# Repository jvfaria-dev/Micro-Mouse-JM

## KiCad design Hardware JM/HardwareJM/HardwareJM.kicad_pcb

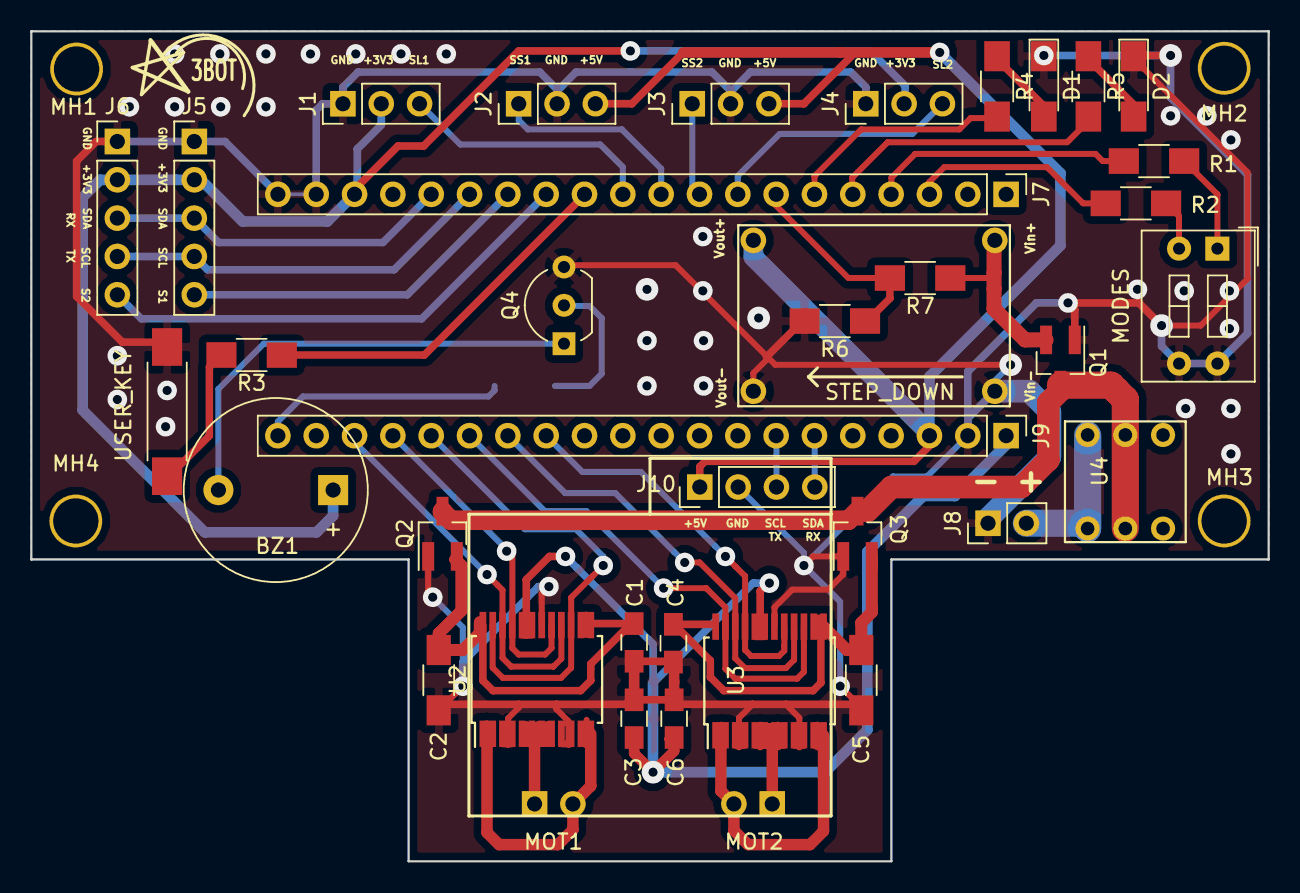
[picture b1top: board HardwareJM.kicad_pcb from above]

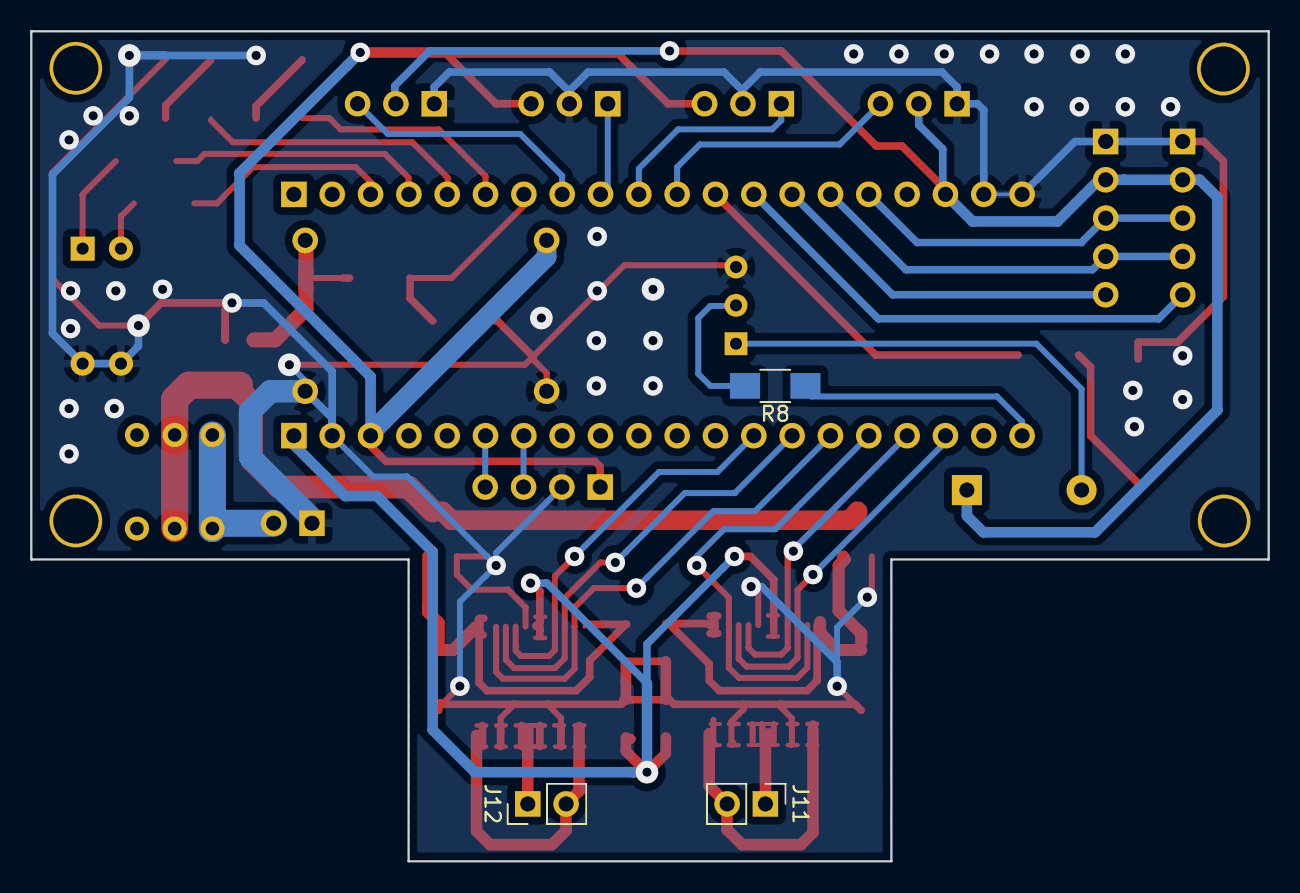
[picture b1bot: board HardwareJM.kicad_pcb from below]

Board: 2 copper layers, 82.0 x 55.0 mm, 43 parts (3 on the bottom side), 42 nets.

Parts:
BZ1: Buzzer; Buzzer_12x9.5RM7.6
C1, C3, C4, C6: C; C_0805_HandSoldering
C2, C5: CP1; C_1206_HandSoldering
D1, D2: LED; LED_1206_HandSoldering
J1: S_LINHA1; Pin_Header_Straight_1x03_Pitch2.54mm
J2: S_SHARP1; Pin_Header_Straight_1x03_Pitch2.54mm
J3: S_SHARP2; Pin_Header_Straight_1x03_Pitch2.54mm
J4: S_LINHA2; Pin_Header_Straight_1x03_Pitch2.54mm
J5: S_LASER1; Pin_Header_Straight_1x05_Pitch2.54mm
J6: S_LASER2; Pin_Header_Straight_1x05_Pitch2.54mm
J7, J9: Conn_01x20; Socket_Strip_Straight_1x20_Pitch2.54mm
J8: BAT; Pin_Header_Straight_1x02_Pitch2.54mm
J10: Conn_01x04; Socket_Strip_Straight_1x04_Pitch2.54mm
J11: MOT1; Pin_Header_Straight_1x02_Pitch2.54mm
J12: MOT2; Pin_Header_Straight_1x02_Pitch2.54mm
MH1: 1; SolderWirePad_single_1-2mmDrill
MH2: 2; SolderWirePad_single_1-2mmDrill
MH3: 3; SolderWirePad_single_1-2mmDrill
MH4: 4; SolderWirePad_single_1-2mmDrill
MODES: SW_DIP_x02; SW_DIP_x2_W7.62mm_Slide
Q1, Q2, Q3: BC817; SOT-23_Handsoldering
Q4: BC337; TO-92_Inline_Wide
R1, R2, R3, R4, R5, R6, R7, R8: R; R_1206_HandSoldering
STEP_DOWN: Step_sown; Step_down
U2, U3: TB6612FNG; SSOP-24_5.3x8.2mm_Pitch0.65mm
U4: KEY
USER_KEY: USER_KEY; SW_SPST_REED_CT05-XXXX-G1

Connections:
+3V3: BZ1.1, C3.1, C6.1, J1.2, J4.2, J5.2, J6.2, J7.18, J9.1, U2.19, U2.20, U3.19, U3.20
+5V: J2.3, J3.3, J9.3, J10.1, STEP_DOWN.4
/S1: J5.5, J7.14
/S2: J6.5, J7.13
/SCL: J5.4, J6.4, J7.15
/SDA: J5.3, J6.3, J7.16
/V+: Q1.2, R7.1, STEP_DOWN.1
/VBAT+: Q1.3, Q2.3, Q3.3, U4.2
/VMOT1: C1.1, C2.1, Q2.2, U2.13, U2.14, U2.24
/VMOT2: C4.1, C5.1, Q3.2, U3.13, U3.14, U3.24
GND: C1.2, C2.2, C3.2, C4.2, C5.2, C6.2, D1.1, D2.1, J1.1, J2.2, J3.2, J4.1, J5.1, J6.1, J7.19, J7.20, J8.1, J9.2, J10.2, MODES.3, MODES.4, Q1.1, Q2.1, Q3.1, Q4.3, R6.2, STEP_DOWN.2, STEP_DOWN.3, U2.3, U2.4, U2.9, U2.10, U2.18, U3.3, U3.4, U3.9, U3.10, U3.18, USER_KEY.1
unnamed: BZ1.2, Q4.1
unnamed: D1.2, R4.1
unnamed: D2.2, R5.1
unnamed: J1.3, J7.11
unnamed: J2.1, J7.10
unnamed: J3.1, J7.9
unnamed: J4.3, J7.8
unnamed: J7.3, R2.2
unnamed: J7.4, R1.2
unnamed: J7.5, R5.2
unnamed: J7.6, R4.2
unnamed: J7.7, R6.1, R7.2
unnamed: J7.12, R3.1
unnamed: J8.2, U4.1
unnamed: J9.13, U3.17, U3.21
unnamed: J9.14, U3.16, U3.22
unnamed: J9.15, U3.15, U3.23
unnamed: J9.16, U2.15, U2.23
unnamed: J9.17, U2.17, U2.21
unnamed: J9.18, U2.16, U2.22
unnamed: J9.20, R8.1
unnamed: J9.7, J10.3
unnamed: J9.6, J10.4
unnamed: J11.1, U2.5, U2.6, U2.7, U2.8
unnamed: J11.2, U2.1, U2.2, U2.11, U2.12
unnamed: J12.1, U3.5, U3.6, U3.7, U3.8
unnamed: J12.2, U3.1, U3.2, U3.11, U3.12
unnamed: Q4.2, R8.2
unnamed: MODES.1, R1.1
unnamed: MODES.2, R2.1
unnamed: R3.2, USER_KEY.2
